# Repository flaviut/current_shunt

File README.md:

# Current shunt

This is a simple current-shunt board designed to make it easy to measure
current with an oscilloscope probe.

## Fabrication

See the releases section for gerbers suitable for building at JLCPCB.

## Building

Putting the device together is simple enough. The only thing that needs explaining is the small disconnected pads next to the 10Ω and 1Ω resistors. The intent is for a thin wire to be connected from the top of the resistor to this pad in order to provide something that approximates a 4-wire connection.

Now that I think about this a bit more, this is overkill, but I'm not planning on producing another copy of this board.

## Case

`case.FCStd` contains a 3d-printable, snap-in case for this board. For a .stl file, see the releases.

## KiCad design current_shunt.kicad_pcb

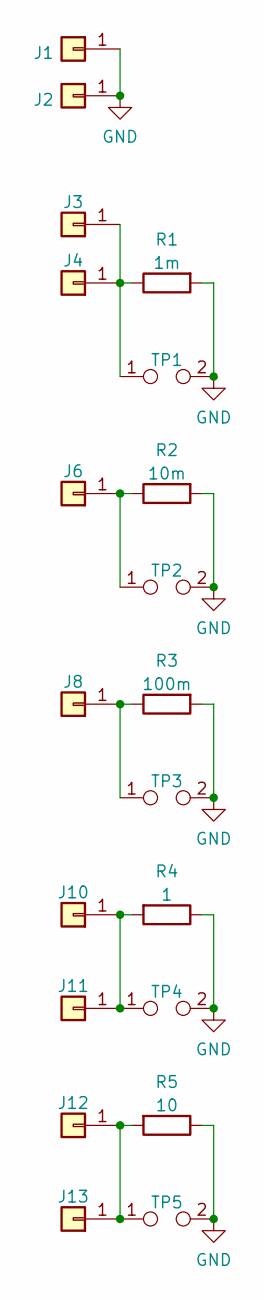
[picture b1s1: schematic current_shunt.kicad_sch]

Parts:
J1, J2: Conn_01x01; Banana_Jack_1Pin; LCSC C106272
J3, J4, J6, J8, J10, J12: Conn_01x01; Banana_Jack_1Pin; LCSC C106273
J11, J13: Conn_01x01; PinHeader_1x01_P1.00mm_Vertical
R1: 1m; R_Shunt_Vishay_WSR2_WSR3; LCSC C2927589
R2: 10m; R_2512_6332Metric; LCSC C500740
R3: 100m; R_2512_6332Metric; LCSC C2994646
R4: 1; R_Axial_DIN0617_L17.0mm_D6.0mm_P7.62mm_Vertical; LCSC C113667
R5: 10; R_Axial_DIN0617_L17.0mm_D6.0mm_P7.62mm_Vertical; LCSC C113667
TP1, TP2, TP3, TP4, TP5: TestPoint_2Pole; TestPoint_2Pads_Pitch2.54mm_Drill1mm

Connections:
GND: J1.1, J2.1, R1.2, R2.2, R3.2, R4.1, R5.1, TP1.2, TP2.2, TP3.2, TP4.2, TP5.2
unnamed: J3.1, J4.1, R1.1, TP1.1
unnamed: J6.1, R2.1, TP2.1
unnamed: J8.1, R3.1, TP3.1
unnamed: J10.1, J11.1, R4.2, TP4.1
unnamed: J12.1, J13.1, R5.2, TP5.1

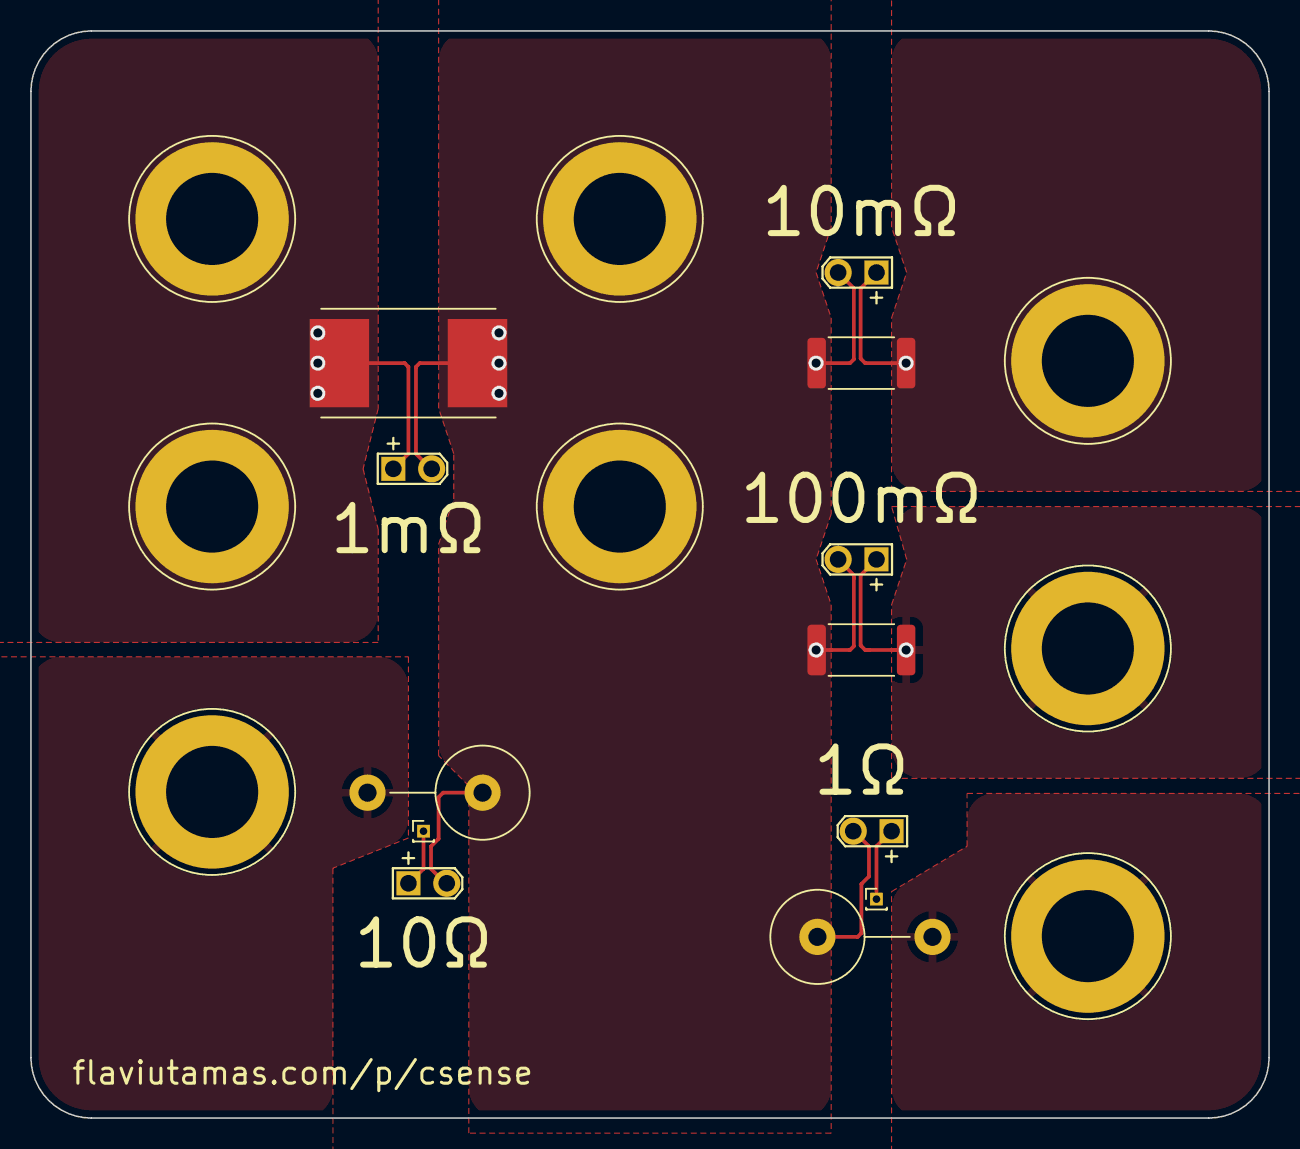
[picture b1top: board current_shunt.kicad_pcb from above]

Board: 2 copper layers, 82.0 x 72.0 mm, 20 parts (0 on the bottom side), 6 nets.

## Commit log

2022-08-26 Cleanups and fixes
2022-11-20 Fix part number
2022-11-20 Add case
2022-11-23 Add readme
2022-11-23 Fix CI
2022-11-23 Add license
